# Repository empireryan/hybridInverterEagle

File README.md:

Hybrid Inverter SDP Eagle Rules. Take pride in your work first and foremost.

#File Naming:
- Directory names will be of the form: 'XX' 
- File names are: XX-v10.brd
- Minor versions will be Thingy-v11, v12, v13. Major will be v20, v30.

#PCB Layout:
- Golden Rule ;) 
	*Never mix Analog and Digital Ground. I repeat - Do not cross the streams! We will connect analog and digital grounds
	in one place only on the final board, using an R0 0805 jumper. Digital grounds should be named DGND, analog grounds should be named AGND.	

	*All VCC, 5V, 3.3V, etc will use appropriate power symbol. Naming conventon will be 3V3 for 3.3V, 1V8 for 1.8V, etc...
	Please make sure to change the values of supply symbols to reflect this nameing/labeling convention.

- Create board frame on 0.05” grid. Make the lower left corner start at 0,0.
- Change line width of the board frame to 0.008”.
- Board frame will be square.
- Change top silkscreen color (tPlace) to gray. Bottom silk (bPlace) to yellow. And tDocu to dark
yellow.
- Every board should have the name printed on the tDocu layer for ease of merging later on
- Stick parts on 0.05” grid. You may not break this rule unless you have a very good reason.
- Label any LED with it's purpose (power, status, D4, Lock, etc).
- Label any connector: Vin, Port1, Batt, 5-9V, etc.
- Label pins where applicable: TX, Power, +, Charge, etc.
- Label switches and switch states: On, USB, etc.
- When applicable, when adding labels, move vias and avoid having vias go through the
silkscreen. Gold phoenix will bump labels around and make the board look bad if a via goes
through the silk.
- Components will be grouped together (the resistors surrounding a transistor in the schematic
will also be together on the PCB).
- Using the autorouter is approved for prototypes.
- Hand routing and touchup of the autorouter is expected for production boards.
- 0.020” vias are allowed. 15mil is minimum.
- Use 10mil traces on designs where possible. 6-8 mil is acceptable. 5 mil is minimum (Asbolute minimum per OshPark 4 layer).
- Use thicker traces for power lines where applicable. 12mil=100mA max, 16mil=500mA, and so
on.
- Spacing is 8mil between traces and space.
- No blind or buried vias.
- Use straight lines with 45degree corners. Avoid 90degree corners (Wire style 3 is good for this)
- Use a ground pour on top/bottom layers where applicable. Power and Ground planes for center layers will be on layers 2 and 15 respectively.  
- Use a 12mil isolation setting on any ground pour. This will help prevent pours from shorting to
traces.
- Load the 4layer.dru file included in the git repo!
Schematic Layout:
- All parts will be on 0.1” grid.
- All GND connections will use GND symbol. 
- Use dashed gray lines to separate a complex design into various smaller bits (for example,
charge circuit, accelerometer, etc).

#Footprints:
- All footprints need >Name (on tNames layer) and >Value (on tValues layer). Size of both will be 0.016”. If you come across a part on a board that doesn't have this, you must change it and save the library.
- All footprints need silkscreen or tDocu indicators showing mechanical sizes, dimensions, or anything weired about the part.
- Silkscreen within a footprint or board should NOT go over pads or metal that will be exposed (it'll flake off easily).
- Every new footprint and part will have a description containing part information and whether the footprint has been proven.
Panelization:
- When panelizing a design, copy original board, paste it into a new PCB. Use a 0.1” grid, and place copies of board exactly 0.020” in between copies (all sides). No indicators for v-scoring are needed.
- Make sure you are aware of any overhanging parts between copies. A bluetooth module antenna could over-run SMD components on the copy next door.
Assembly Sheet:
- All assembly sheets will be in PDF form
- All assembly sheets will have version number in tValue text below the design 45) Every part will have value next to the component. Text size should be 0.016” 46) LEDs must have color indicated
- Any component not to be populated will have a large 'DNP' label on part.

#Printing Schematics:
- Print to PDF by hitting the PDF button in Eagle print window 49) Make sure 'Rotate' is NOT checked
- Make sure 'Caption' is NOT checked
- Select Sheets : 'All' to print all sheets
- Scale factor 1

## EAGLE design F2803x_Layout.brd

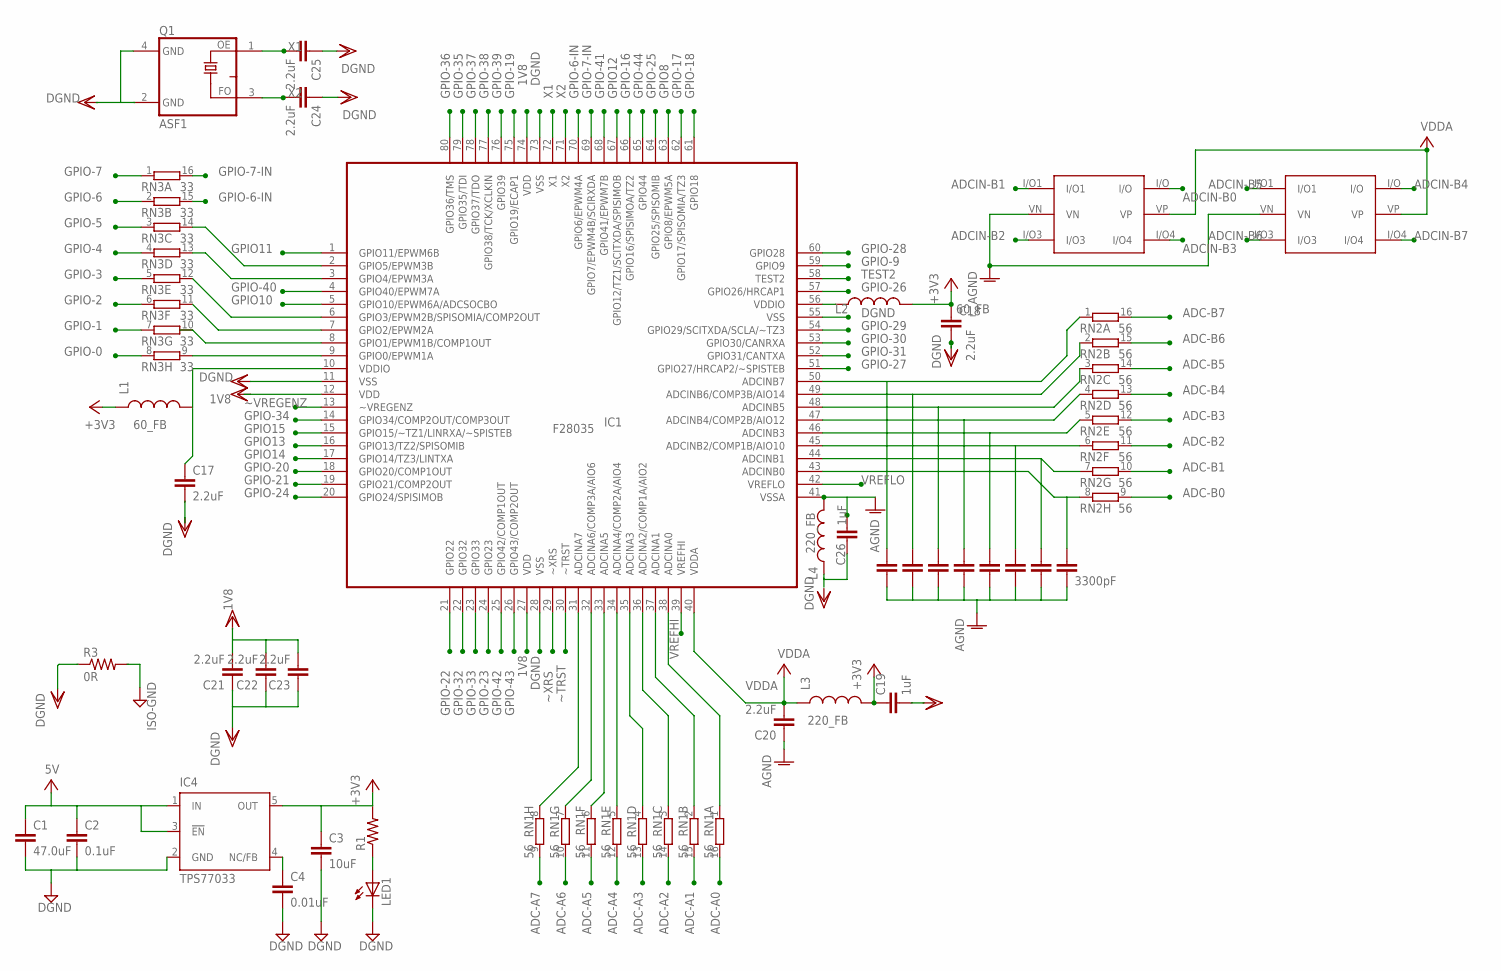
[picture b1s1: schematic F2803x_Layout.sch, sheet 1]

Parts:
C1: 47.0uF; 0805
C2: 0.1uF; 0603-CAP
C3, C7, C10, C11, C12, C13, C14, C15: 10uF; 0603-CAP
C4: 0.01uF; 0603-CAP
C16: 3300pF; 0603-CAP
C17, C18, C20, C21, C22, C23, C24, C25: 2.2uF; 0603-CAP
C19, C26: 1uF; 0603-CAP
IC1: F28035; PN_S-PQFP-G80
IC4: TPS77033; SOT23-DBV
L1, L2: 60_FB; 0805
L3, L4: 220_FB; 0805
LED1: LEDCHIPLED_0603; CHIPLED_0603
Q1: ASF1; ASF
R1: RESISTOR0603; 0603-RES
R3: 0R; 0805
RN1, RN2: 56; EXB2HV
RN3: 33; EXB2HV
U$1, U$2: NUP4201MR6; SOT23-6L

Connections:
1V8: C21.2, C22.2, C23.2, IC1.12 (VDD), IC1.27 (VDD), IC1.74 (VDD)
3V3: C3.1, C18.1, C19.1, IC4.5 (OUT), L1.1, L2.2, L3.2, R1.2; also elsewhere on the board
5V: C1.1, C2.1, IC4.1 (IN), IC4.3 (!EN)
ADC-A0: RN1.16 (2)
ADC-A1: RN1.15 (2)
ADC-A2: RN1.14 (2)
ADC-A3: RN1.13 (2)
ADC-A4: RN1.12 (2)
ADC-A5: RN1.11 (2)
ADC-A6: RN1.10 (2)
ADC-A7: RN1.9 (2)
ADC-B0: RN2.9 (2)
ADC-B1: RN2.10 (2)
ADC-B2: RN2.11 (2)
ADC-B3: RN2.12 (2)
ADC-B4: RN2.13 (2)
ADC-B5: RN2.14 (2)
ADC-B6: RN2.15 (2)
ADC-B7: RN2.16 (2)
ADCIN-B0: C16.1, IC1.43 (ADCINB0), RN2.8 (1), U$1.I/O
ADCIN-B1: C15.1, IC1.44 (ADCINB1), RN2.7 (1), U$1.I/O1
ADCIN-B2: C14.1, IC1.45 (ADCINB2/COMP1B/AIO10), RN2.6 (1), U$1.I/O3
ADCIN-B3: C13.1, IC1.46 (ADCINB3), RN2.5 (1), U$1.I/O4
ADCIN-B4: C12.1, IC1.47 (ADCINB4/COMP2B/AIO12), RN2.4 (1), U$2.I/O
ADCIN-B5: C11.1, IC1.48 (ADCINB5), RN2.3 (1), U$2.I/O1
ADCIN-B6: C10.1, IC1.49 (ADCINB6/COMP3B/AIO14), RN2.2 (1), U$2.I/O3
ADCIN-B7: U$2.I/O4
ADCINB7: C7.1, IC1.50 (ADCINB7), RN2.1
AGND: C7.2, C10.2, C11.2, C12.2, C13.2, C14.2, C15.2, C16.2, C20.1, IC1.41 (VSSA), L4.2, U$1.VN, U$2.VN
DGND: C1.2, C2.2, C3.2, C4.2, C18.2, C22.1, C23.1, C24.1, C25.1, C26.1, IC1.11 (VSS), IC1.28 (VSS), IC1.55 (VSS), IC1.73 (VSS), IC4.2 (GND), L4.1, LED1.C, Q1.4 (VCC); also elsewhere on the board
GPIO8: IC1.63 (GPIO8/EPWM5A)
GPIO10: IC1.5 (GPIO10/EPWM6A/ADCSOCBO)
GPIO11: IC1.1 (GPIO11/EPWM6B)
GPIO12: IC1.67 (GPIO12/TZ1/SCITXDA/SPISIMOB)
GPIO13: IC1.16 (GPIO13/TZ2/SPISOMIB)
GPIO14: IC1.17 (GPIO14/TZ3/LINTXA)
GPIO15: IC1.15 (GPIO15/~TZ1/LINRXA/~SPISTEB)
GPIO-0: RN3.8 (1)
GPIO-1: RN3.7 (1)
GPIO-2: RN3.6 (1)
GPIO-3: RN3.5 (1)
GPIO-4: RN3.4 (1)
GPIO-5: RN3.3 (1)
GPIO-6: RN3.2 (1)
GPIO-6-IN: IC1.70 (GPIO6/EPWM4A), RN3.15 (2)
GPIO-7: RN3.1
GPIO-7-IN: IC1.69 (GPIO7/EPWM4B/SCIRXDA), RN3.16 (2)
GPIO-9: IC1.59 (GPIO9)
GPIO-16: IC1.66 (GPIO16/SPISIMOA/TZ2)
GPIO-17: IC1.62 (GPIO17/SPISOMIA/TZ3)
GPIO-18: IC1.61 (GPIO18)
GPIO-19: IC1.75 (GPIO19/ECAP1)
GPIO-20: IC1.18 (GPIO20/COMP1OUT)
GPIO-21: IC1.19 (GPIO21/COMP2OUT)
GPIO-22: IC1.21 (GPIO22)
GPIO-23: IC1.24 (GPIO23)
GPIO-24: IC1.20 (GPIO24/SPISIMOB)
GPIO-25: IC1.64 (GPIO25/SPISOMIB)
GPIO-26: IC1.57 (GPIO26/HRCAP1)
GPIO-27: IC1.51 (GPIO27/HRCAP2/~SPISTEB)
GPIO-28: IC1.60 (GPIO28); also elsewhere on the board
GPIO-29: IC1.54 (GPIO29/SCITXDA/SCLA/~TZ3); also elsewhere on the board
GPIO-30: IC1.53 (GPIO30/CANRXA)
GPIO-31: IC1.52 (GPIO31/CANTXA); also elsewhere on the board
GPIO-32: IC1.22 (GPIO32)
GPIO-33: IC1.23 (GPIO33)
GPIO-34: IC1.14 (GPIO34/COMP2OUT/COMP3OUT); also elsewhere on the board
GPIO-35: IC1.79 (GPIO35/TDI)
GPIO-36: IC1.80 (GPIO36/TMS)
GPIO-37: IC1.78 (GPIO37/TDO)
GPIO-38: IC1.77 (GPIO38/TCK/XCLKIN)
GPIO-39: IC1.76 (GPIO39)
GPIO-40: IC1.4 (GPIO40/EPWM7A)
GPIO-41: IC1.68 (GPIO41/EPWM7B)
GPIO-42: IC1.25 (GPIO42/COMP1OUT)
GPIO-43: IC1.26 (GPIO43/COMP2OUT)
GPIO-44: IC1.65 (GPIO44)
ISO-GND: Q1.2 (GND); also elsewhere on the board
unnamed: IC1.38 (ADCINA0), RN1.1
unnamed: IC1.37 (ADCINA1), RN1.2 (1)
unnamed: IC1.36 (ADCINA2/COMP1A/AIO2), RN1.3 (1)
unnamed: IC1.35 (ADCINA3), RN1.4 (1)
unnamed: IC1.34 (ADCINA4/COMP2A/AIO4), RN1.5 (1)
unnamed: IC1.33 (ADCINA5), RN1.6 (1)
unnamed: IC1.32 (ADCINA6/COMP3A/AIO6), RN1.7 (1)
unnamed: IC1.31 (ADCINA7), RN1.8 (1)
unnamed: IC1.9 (GPIO0/EPWM1A), RN3.9 (2)
unnamed: IC1.7 (GPIO2/EPWM2A), RN3.11 (2)
unnamed: IC1.6 (GPIO3/EPWM2B/SPISOMIA/COMP2OUT), RN3.12 (2)
unnamed: IC1.3 (GPIO4/EPWM3A), RN3.13 (2)
unnamed: IC1.2 (GPIO5/EPWM3B), RN3.14 (2)
unnamed: IC1.56 (VDDIO), L2.1
unnamed: IC1.10 (VDDIO), L1.2
unnamed: LED1.A, R1.1
unnamed: C4.1, IC4.4 (NC/FB)
TEST2: IC1.58 (TEST2)
VDDA: C20.2, IC1.40 (VDDA), L3.1, U$1.VP, U$2.VP; also elsewhere on the board
VREFHI: IC1.39 (VREFHI); also elsewhere on the board
VREFLO: IC1.42 (VREFLO); also elsewhere on the board
X1: C25.2, IC1.72 (X1), Q1.1 (OE)
X2: IC1.71 (X2)
~TRST: IC1.30 (~TRST)
~VREGENZ: IC1.13 (~VREGENZ)
~XRS: IC1.29 (~XRS)

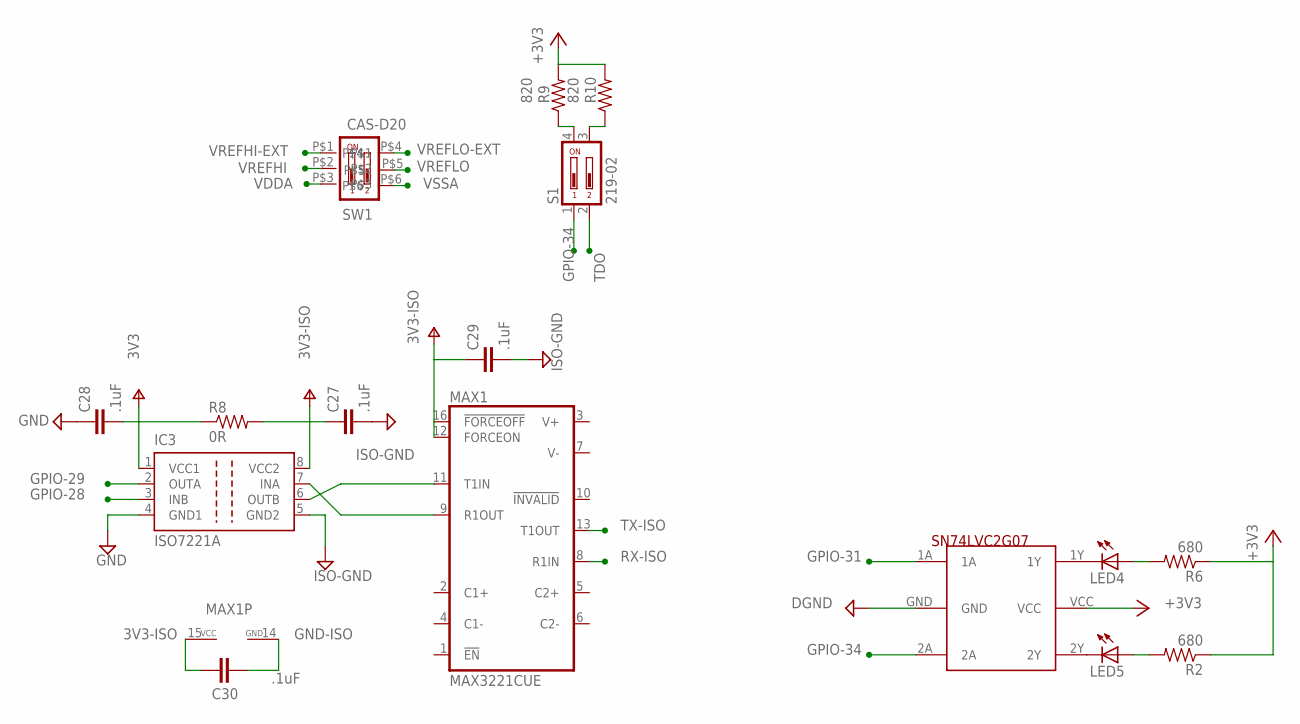
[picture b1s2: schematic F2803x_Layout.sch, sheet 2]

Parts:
C27, C28, C29, C30: .1uF; 0603-CAP
IC3: ISO7221A; SO-08
LED4, LED5: LEDCHIPLED_0603; CHIPLED_0603
MAX1: MAX3221CUE; TSSOP16
R2, R6: 680; 0603-RES
R8: 0R; 0805
R9, R10: 820; 0603-RES
S1: 219-02; CTS-219-02
SW1: CAS-D20
U$4: SN74LVC2G07; SOT23-6L

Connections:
3V3: C28.2, IC3.1 (VCC1), R8.1, U$4.VCC; also elsewhere on the board
3V3-ISO: C27.1, C29.1, C30.1, IC3.8 (VCC2), MAX1.12 (FORCEON), MAX1.15 (VCC), MAX1.16 (!FORCEOFF), R8.2
+3V3: R2.1, R6.1, R9.2, R10.2
DGND: U$4.GND; also elsewhere on the board
GND: C27.2, C28.1, C29.2, IC3.4 (GND1)
GND-ISO: C30.2, MAX1.14 (GND)
GPIO-28: IC3.3 (INB); also elsewhere on the board
GPIO-29: IC3.2 (OUTA); also elsewhere on the board
GPIO-31: U$4.1A; also elsewhere on the board
GPIO-34: S1.1, U$4.2A; also elsewhere on the board
ISO-GND: IC3.5 (GND2); also elsewhere on the board
unnamed: IC3.7 (INA), MAX1.9 (R1OUT)
unnamed: IC3.6 (OUTB), MAX1.11 (T1IN)
unnamed: R9.1, S1.4
unnamed: R10.1, S1.3
unnamed: LED4.C, U$4.1Y
unnamed: LED5.C, U$4.2Y
unnamed: LED4.A, R6.2
unnamed: LED5.A, R2.2
RX-ISO: MAX1.8 (R1IN)
TDO: S1.2
TX-ISO: MAX1.13 (T1OUT)
VDDA: SW1.P$3; also elsewhere on the board
VREFHI: SW1.P$2; also elsewhere on the board
VREFHI-EXT: SW1.P$1
VREFLO: SW1.P$5; also elsewhere on the board
VREFLO-EXT: SW1.P$4
VSSA: SW1.P$6

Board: 2 copper layers, 53 parts (0 on the bottom side), 53 nets, no tracks yet.

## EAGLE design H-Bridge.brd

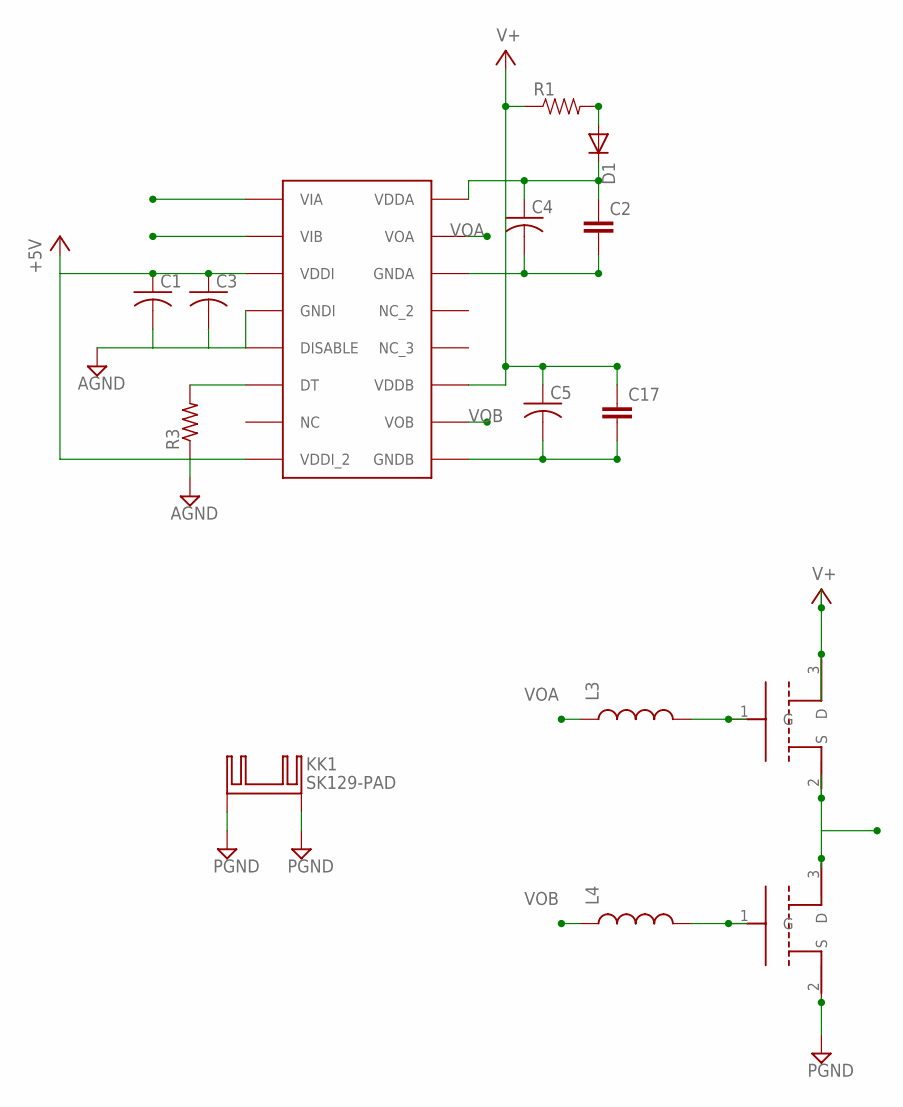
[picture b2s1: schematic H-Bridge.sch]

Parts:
C1, C3: C-USC0603K; C0603K
C2, C17: CAP0805; 0805
C4, C5: C-USC0805K; C0805K
D1: DIODE-DO214BA; DO214BA
KK1: SK129-PAD; SK129
L3, L4: INDUCTOR0805; 0805
R1: RESISTOR0805-RES; 0805
R3: R-US_R0603; R0603
U$2: MCP3008_ADC; SOIC16
U$3, U$4: HEMT-FET; TO220V

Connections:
+5V: C1.1, C3.1, U$2.VDDI, U$2.VDDI_2
AGND: C1.2, C3.2, R3.1, U$2.DISABLE, U$2.GNDI
GNDA: C2.2, C4.2, U$2.GNDA, U$3.3 (D), U$4.2 (S)
unnamed: D1.A, R1.2
unnamed: C2.1, C4.1, D1.C, U$2.VDDA
unnamed: L3.2, U$4.1 (G)
unnamed: L4.2, U$3.1 (G)
unnamed: R3.2, U$2.DT
PGND: C5.2, C17.2, KK1.A2,5, KK1.B2,5, U$2.GNDB, U$3.2 (S)
V+: C5.1, C17.1, R1.1, U$2.VDDB
VIA: U$2.VIA
VIB: U$2.VIB
VOA: L3.1, U$2.VOA
VOB: L4.1, U$2.VOB

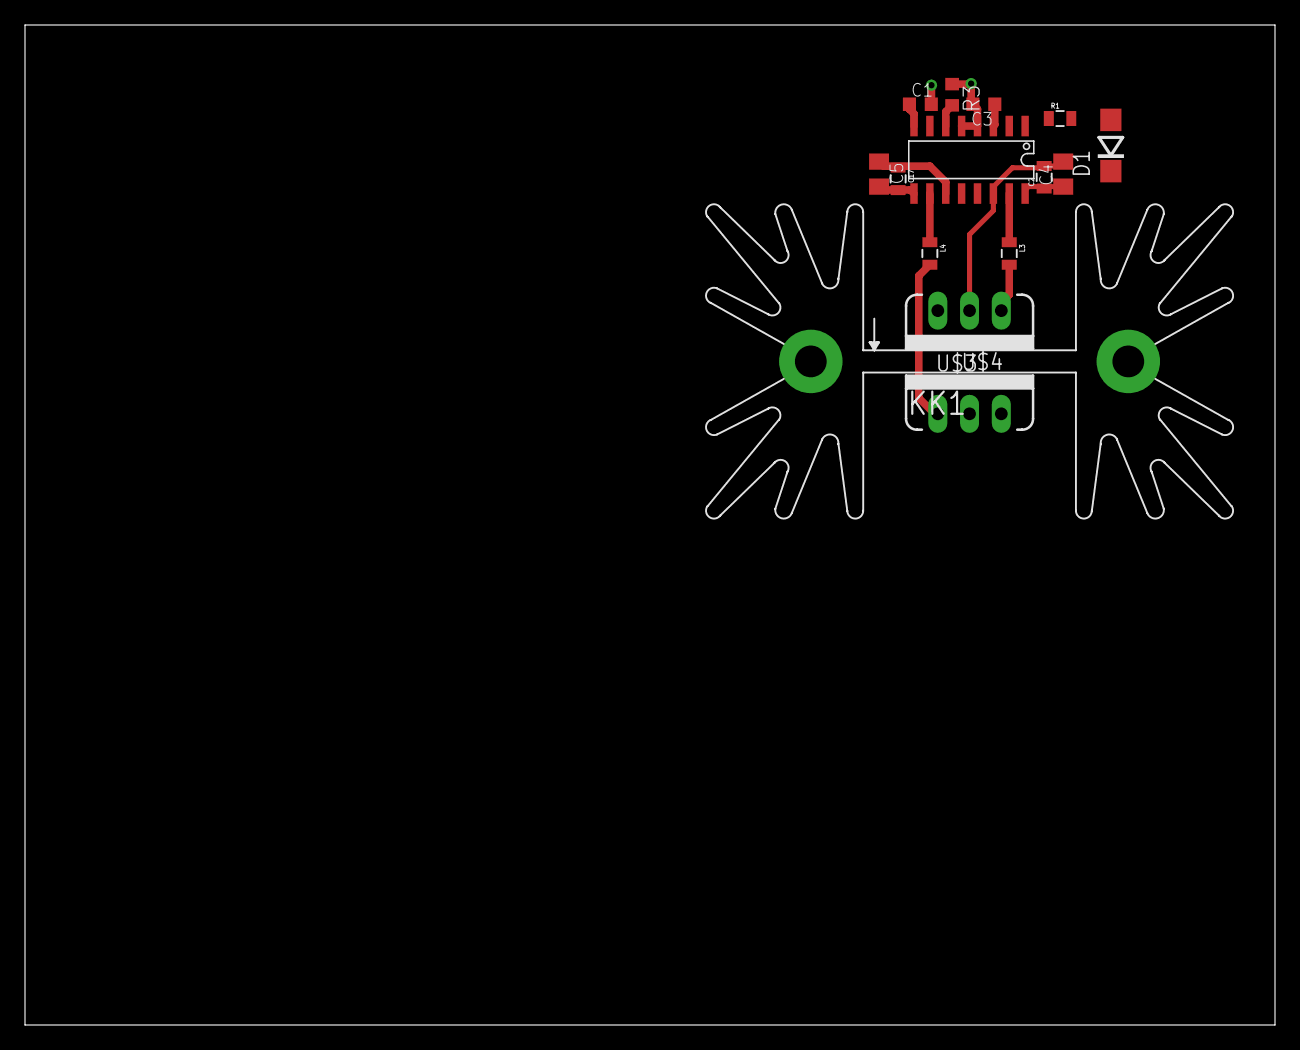
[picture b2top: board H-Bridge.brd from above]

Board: 2 copper layers, 100.0 x 80.0 mm, 15 parts (0 on the bottom side), 12 nets.

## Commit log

2015-02-24 Initial commit for hybridInverter PCB files in eagle
2015-02-24 Replaced original .dru file with correct .dru for 4 layer boards

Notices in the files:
parts and their libraries:
SparkFun-Passives: Licensing: Creative Commons ShareAlike 4.0 International - https://creativecommons.org/licenses/by-sa/4.0
